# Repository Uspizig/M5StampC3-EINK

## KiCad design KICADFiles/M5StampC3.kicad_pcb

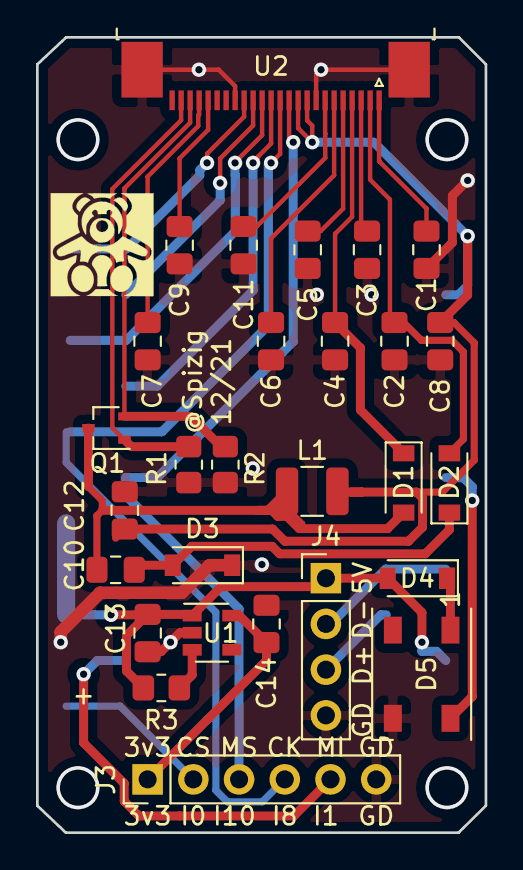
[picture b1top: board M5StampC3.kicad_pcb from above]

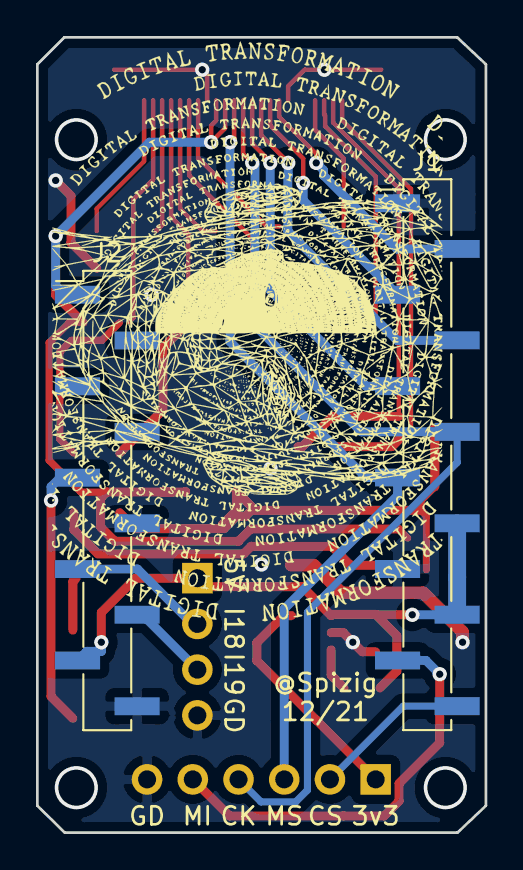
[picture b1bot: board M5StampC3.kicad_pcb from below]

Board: 2 copper layers, 24.9 x 44.2 mm, 30 parts (2 on the bottom side), 30 nets.

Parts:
C1, C2, C3, C4, C5, C6, C7, C9, C11: 105; C_0805_2012Metric_Pad1.18x1.45mm_HandSolder
C8: 104; C_0805_2012Metric_Pad1.18x1.45mm_HandSolder
C10, C12, C13: 4.7uF50V; C_0805_2012Metric_Pad1.18x1.45mm_HandSolder
C14: 100n; C_0805_2012Metric_Pad1.18x1.45mm_HandSolder
D1, D2, D3, D4: MBR0530; D_SOD-123
D5: WS2812B; LED_WS2812B_PLCC4_5.0x5.0mm_P3.2mm
J1: Conn_01x12_Male; PinHeader_1x12_P2.54mm_Vertical_SMD_Pin1Left
J2: Conn_01x10_Male; PinHeader_1x10_P2.54mm_Vertical_SMD_Pin1Left
J3: Conn_01x06_Male; PinHeader_1x06_P2.54mm_Vertical
J4: Conn_01x04_Male; PinHeader_1x04_P2.54mm_Vertical
L1: 68uH1A; L_1210_3225Metric
Q1: Si1308; SOT-323_SC-70
R1, R3: 10K; R_0805_2012Metric_Pad1.20x1.40mm_HandSolder
R2: 0.47R; R_0805_2012Metric_Pad1.20x1.40mm_HandSolder
U1: RT9013; SOT-23-5
U2: FPCConn; TE_2-1734839-4_1x24-1MP_P0.5mm_Horizontal

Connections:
+3.3VA: C14.1, J3.1, U1.5
+3.3VP: C8.2, C12.2, J2.1, L1.2, U2.9, U2.10
+5V: C13.1, D4.2, J1.8, J1.10, J2.9, J4.1, R3.1, U1.1
/D+: J2.8, J4.3
/D-: J2.7, J4.2
/EPD_BUSY: J1.2, U2.16
/EPD_CLK: J1.6, J3.4, U2.12
/EPD_CS: J1.5, U2.13
/EPD_DC: J1.4, U2.14
/EPD_MOSI: J1.7, J3.3, U2.11
/EPD_RST: J1.3, U2.15
/G0: J1.12, J3.2
/G1: J1.11, J3.5
/G9: D5.4, J2.5
GND: C1.1, C2.1, C3.1, C4.1, C5.1, C6.1, C7.1, C8.1, C9.1, C11.1, C12.1, C13.2, C14.2, D3.1, D5.3, J1.1, J1.9, J2.6, J2.10, J3.6, J4.4, R1.2, R2.2, U1.2, U2.8, U2.17, U2.MP
unnamed: C1.2, U2.1
unnamed: C2.2, D2.2, U2.2
unnamed: C3.2, U2.3
unnamed: C4.2, D1.1, U2.4
unnamed: C5.2, U2.5
unnamed: C6.2, U2.6
unnamed: C7.2, U2.21
unnamed: C9.2, U2.20
unnamed: C10.1, D1.2, L1.1, Q1.3
unnamed: C10.2, D2.1, D3.2
unnamed: C11.2, U2.7
unnamed: D4.1, D5.1
unnamed: Q1.1, R1.1, U2.23
unnamed: Q1.2, R2.1, U2.22
unnamed: R3.2, U1.3

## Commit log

2022-01-07 Version 2 with LORA
